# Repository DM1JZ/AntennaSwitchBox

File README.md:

# AntennaSwitchBox

This is a 2x2 antenna switching matrix based on HF53 relays. First draft, not testet yet (V1.0).

RF power should be at least 50 W.
The matrix is controlled by push keys or by UART commands via the STM32 microcontroller.

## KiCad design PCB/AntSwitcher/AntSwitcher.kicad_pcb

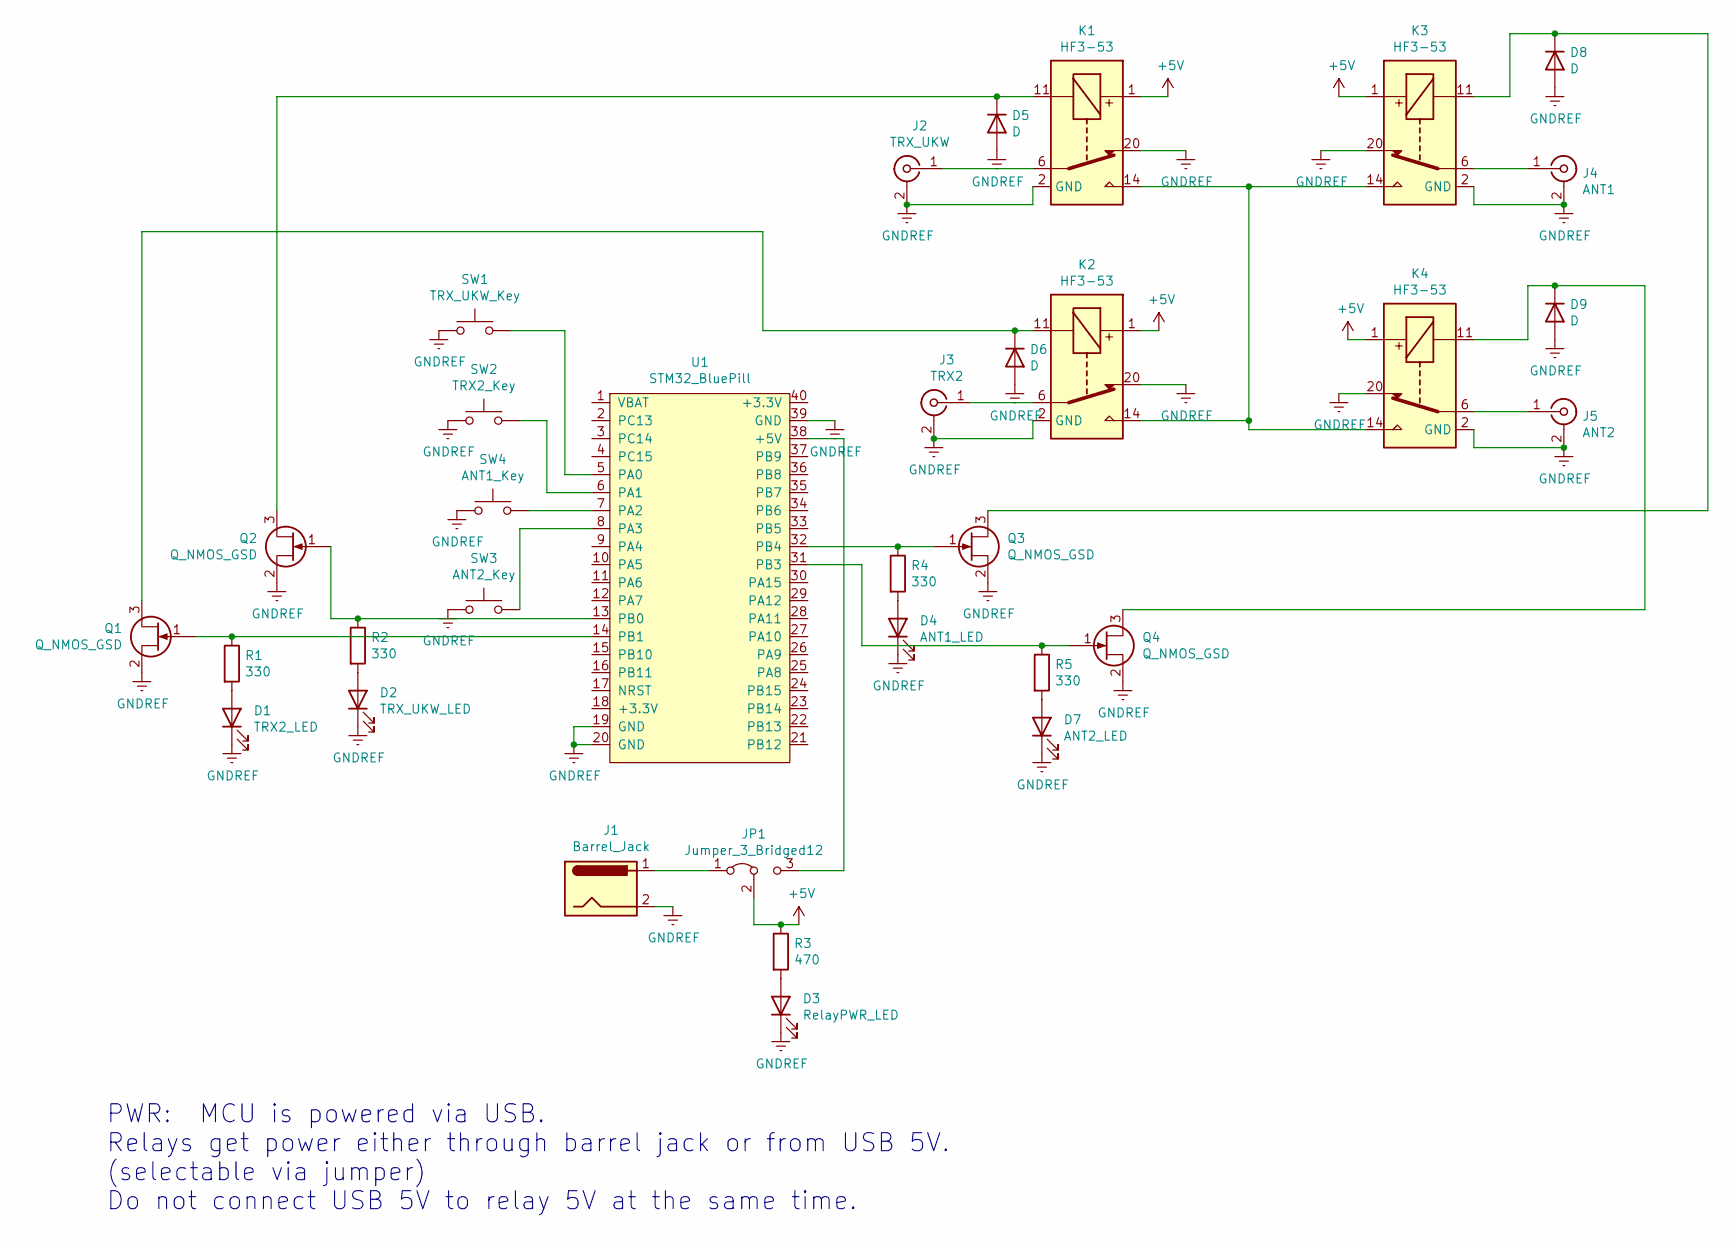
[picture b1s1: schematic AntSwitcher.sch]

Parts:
D1: TRX2_LED; LED_D5.0mm
D2: TRX_UKW_LED; LED_D5.0mm
D3: RelayPWR_LED; LED_D5.0mm
D4: ANT1_LED; LED_D5.0mm
D5, D6, D8, D9: D; SOT-23
D7: ANT2_LED; LED_D5.0mm
J1: Barrel_Jack; BarrelJackSMD
J2: TRX_UKW; Molex_SMA_Jack_Edge_Mount
J3: TRX2; Molex_SMA_Jack_Edge_Mount
J4: ANT1; Molex_SMA_Jack_Edge_Mount
J5: ANT2; Molex_SMA_Jack_Edge_Mount
JP1: Jumper_3_Bridged12; Pin_Header_Straight_1x03_Pitch2.54mm
K1, K2, K3, K4: HF3-53; Relay_SPDT_AXICOM_HF3Series_50ohms_Pitch1.27mm
Q1, Q2, Q3, Q4: Q_NMOS_GSD; SOT-23
R1, R2, R4, R5: 330; R_0603
R3: 470; R_0603
SW1: TRX_UKW_Key; SW_PUSH_6mm
SW2: TRX2_Key; SW_PUSH_6mm
SW3: ANT2_Key; SW_PUSH_6mm
SW4: ANT1_Key; SW_PUSH_6mm
U1: STM32_BluePill

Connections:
+5V: JP1.2 (C), K1.1, K2.1, K3.1, K4.1, R3.1
GNDREF: D1.1 (K), D2.1 (K), D3.1 (K), D4.1 (K), D5.1 (A), D6.1 (A), D7.1 (K), D8.1 (A), D9.1 (A), J1.2, J2.2 (Ext), J3.2 (Ext), J4.2 (Ext), J5.2 (Ext), K1.2 (GND), K1.5 (GND), K1.7 (GND), K1.10 (GND), K1.12 (GND), K1.13 (GND), K1.15 (GND), K1.17 (GND), K1.19 (GND), K1.20, K1.21 (GND), K1.22 (GND), K2.2 (GND), K2.5 (GND), K2.7 (GND), K2.10 (GND), K2.12 (GND), K2.13 (GND), K2.15 (GND), K2.17 (GND), K2.19 (GND), K2.20, K2.21 (GND), K2.22 (GND), K3.2 (GND), K3.5 (GND), K3.7 (GND), K3.10 (GND), K3.12 (GND), K3.13 (GND), K3.15 (GND), K3.17 (GND), K3.19 (GND), K3.20, K3.21 (GND), K3.22 (GND), K4.2 (GND), K4.5 (GND), K4.7 (GND), K4.10 (GND), K4.12 (GND), K4.13 (GND), K4.15 (GND), K4.17 (GND), K4.19 (GND), K4.20, K4.21 (GND), K4.22 (GND), Q1.2 (S), Q2.2 (S), Q3.2 (S), Q4.2 (S), SW1.1, SW2.1, SW3.1, SW4.1, U1.19 (GND), U1.20 (GND), U1.39 (GND)
unnamed: D1.2 (A), R1.2
unnamed: D2.2 (A), R2.2
unnamed: D3.2 (A), R3.2
unnamed: D4.2 (A), R4.2
unnamed: D5.3 (K), K1.11, Q2.3 (D)
unnamed: D6.3 (K), K2.11, Q1.3 (D)
unnamed: D7.2 (A), R5.2
unnamed: D8.3 (K), K3.11, Q3.3 (D)
unnamed: D9.3 (K), K4.11, Q4.3 (D)
unnamed: J1.1, JP1.1 (A)
unnamed: J2.1 (In), K1.6
unnamed: J3.1 (In), K2.6
unnamed: J4.1 (In), K3.6
unnamed: J5.1 (In), K4.6
unnamed: JP1.3 (B), U1.38 (+5V)
unnamed: K1.14, K2.14, K3.14, K4.14
unnamed: Q1.1 (G), R1.1, U1.14 (PB1)
unnamed: Q2.1 (G), R2.1, U1.13 (PB0)
unnamed: Q3.1 (G), R4.1, U1.32 (PB4)
unnamed: Q4.1 (G), R5.1, U1.31 (PB3)
unnamed: SW1.2, U1.5 (PA0)
unnamed: SW2.2, U1.6 (PA1)
unnamed: SW3.2, U1.8 (PA3)
unnamed: SW4.2, U1.7 (PA2)

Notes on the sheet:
PWR: MCU is powered via USB. Relays get power either through barrel jack or from USB 5V. (selectable via jumper) Do not connect USB 5V to relay 5V at the same time.

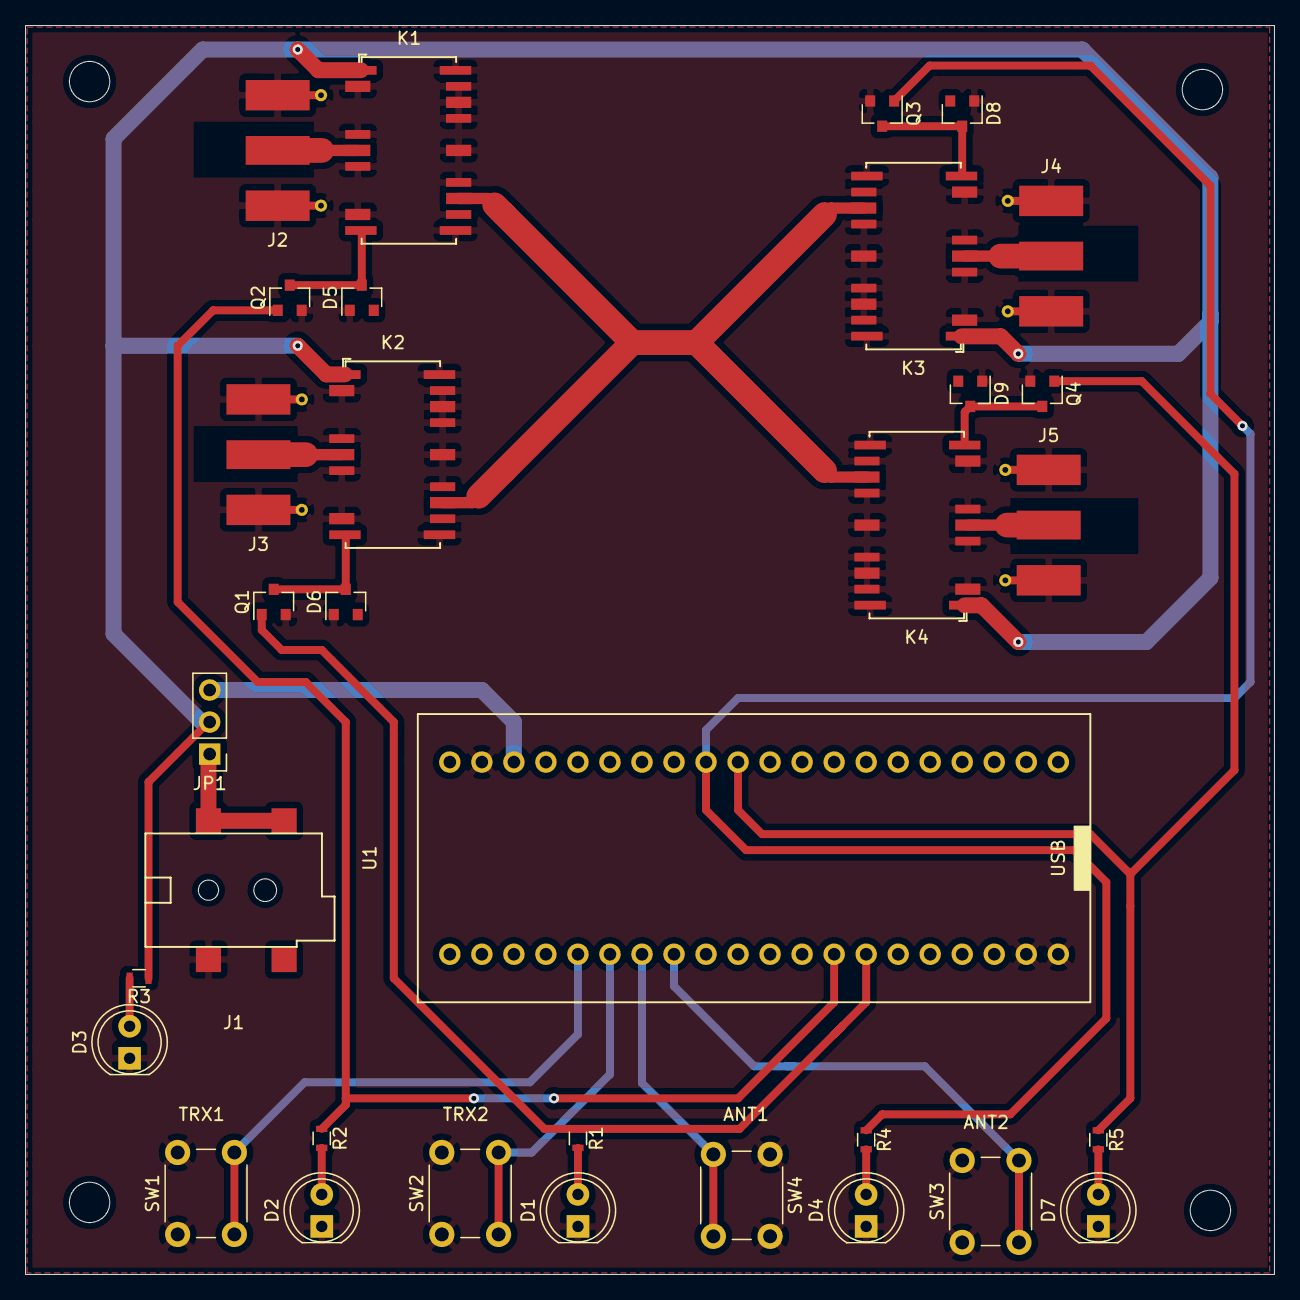
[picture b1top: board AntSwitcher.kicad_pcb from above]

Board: 2 copper layers, 99.1 x 99.1 mm, 33 parts (0 on the bottom side), 26 nets.

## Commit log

2020-06-20 Datsheets, List of components
2020-06-20 Schematics, Layout first sort out
2020-07-06 HF-Layout Relays
2020-07-12 Layout components placement
2020-08-01 Layout Routing draft
2020-08-01 Layout final
2020-08-02 Readme added
2020-08-02 License file added
2020-08-05 Barrel Jack changed to SMD variant
